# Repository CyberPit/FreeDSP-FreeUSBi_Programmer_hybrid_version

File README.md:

# FreeDSP-FreeUSBi_Programmer_hybrid_version　　

This is another PCB layout design of FreeUSBi.  
Component Layout had changed, Voltage-shifter design changed, selectable parts type capability (SMD or TH)
Please see the images in the "Photo" directory for differences.  
  
## Issue found on some CY7C68013A boards.
Some CY7C68013A boards can not boot when connected to a FreeUSBi board. The reason is that the SDA line of the I2C bus voltage dropped during the boot sequence. The Voltage-Shifter circuit control line and I2C pull-up circuit were not tied to 3.3V because the uP has not run yet. So, the version 0.5 design connects them to a regulated 3.3V line. According to this change, the I2C line is pulled up to 3.3V anytime a USB is connected.  
  
## For Windows 10 users, Info:
Some machines were not able to run the official FreeUSBi driver.  
But a few machines have succeeded in installing & running with the 3eAudio version FreeUSBi driver (Located at https://www.3e-audio.com/dsp/adau1701-2in4out/)

# License
This work and all other materials under https://github.com/freeDSP are licensed under a Creative Commons Attribution Share-Alike 4.0 license. This allows for both personal and commercial derivative works, as long as they credit freeDSP and release their designs under the same license.

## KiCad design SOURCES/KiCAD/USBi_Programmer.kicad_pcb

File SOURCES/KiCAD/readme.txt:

Here is another version of FreeUSBi.
- Same Function
- New Layout PCB
- Selectable SMD/TH resisitors

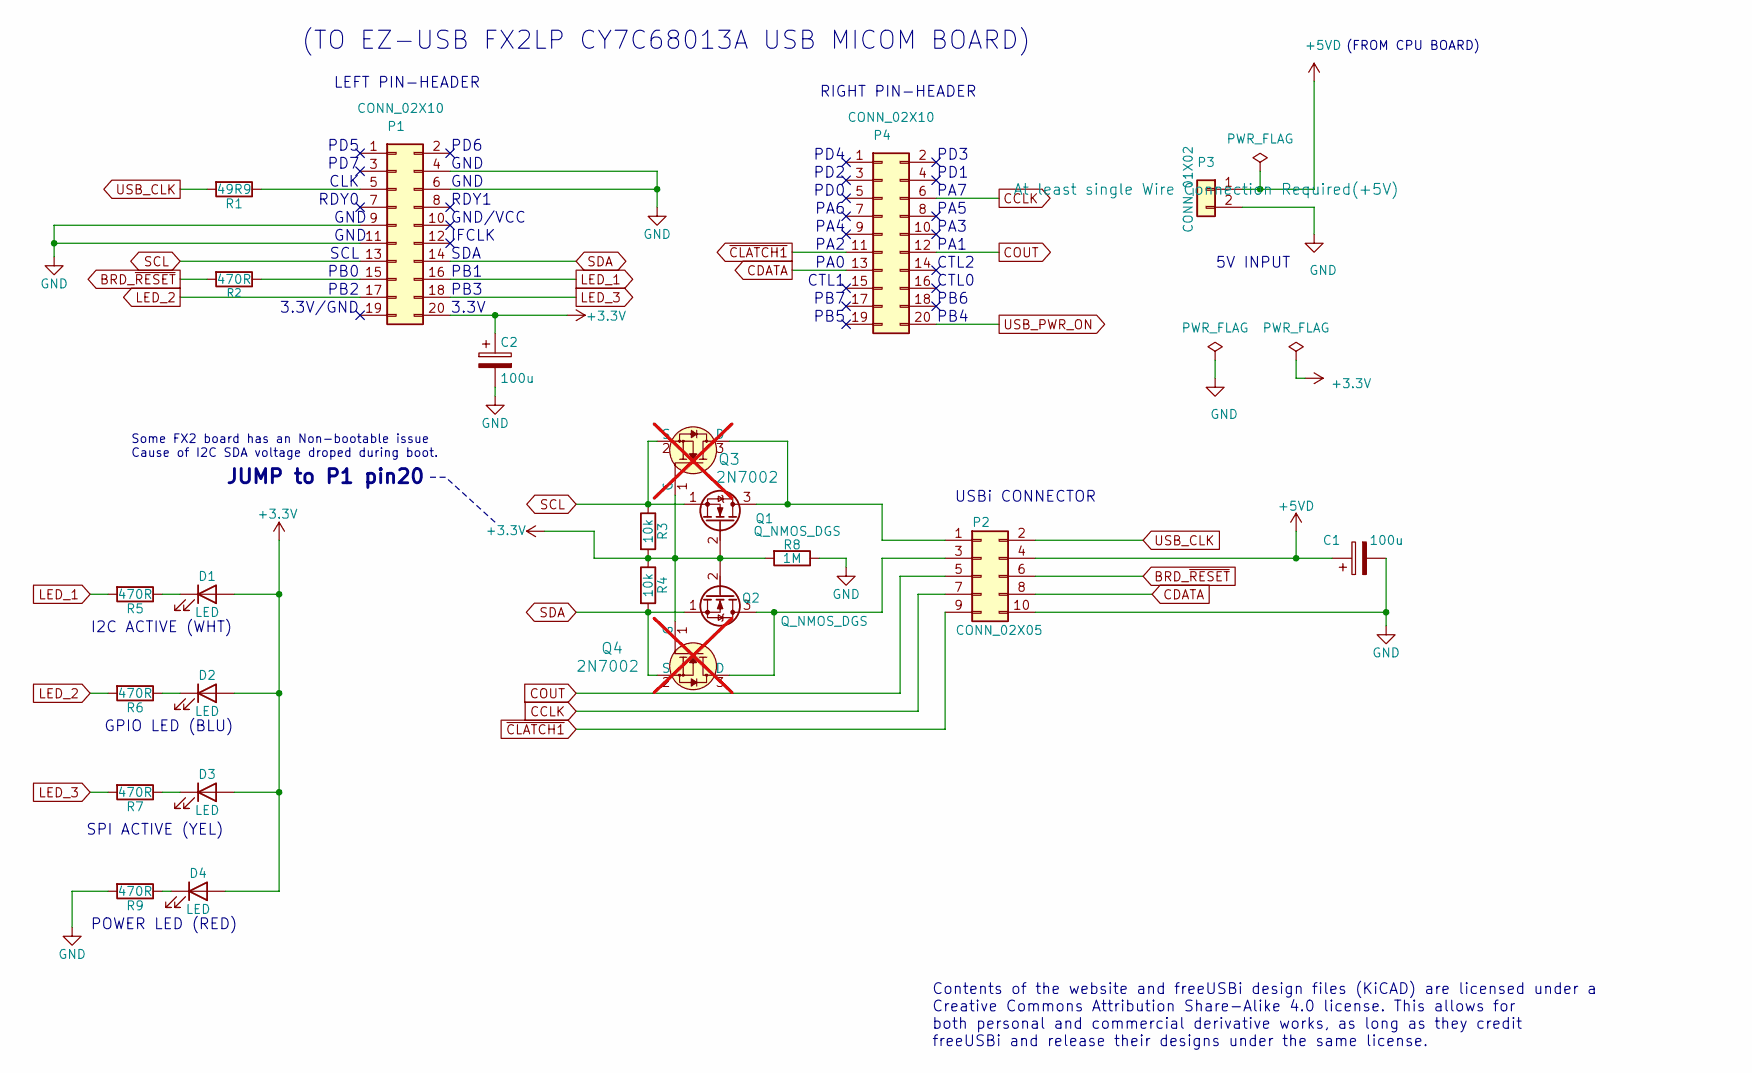
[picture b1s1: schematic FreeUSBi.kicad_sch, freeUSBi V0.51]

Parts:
C1, C2: 100u; Elko_vert_11.2x6.3mm_RM2.5_CopperClear
D1, D2, D3, D4: LED; LED_D3.0mm
P1, P4: CONN_02X10; Pin_Header_Straight_2x10
P2: CONN_02X05; IDC_Header_Straight_10pins
P3: CONN_01X02; Pin_Header_Straight_1x02
Q1, Q2: Q_NMOS_DGS; TO-92_Inline_Narrow_Oval
Q3, Q4: 2N7002; SOT-23-3; MPN 2N7002; Digi-Key_PN 2N7002NCT-ND; not fitted
R1: 49R9; Resistor_SMD+THTuniversal_0603to0805_RM7.5_HandSoldering_Re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
R2, R5, R6, R7, R9: 470R; Resistor_SMD+THTuniversal_0603to0805_RM7.5_HandSoldering_Re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
R3, R4: 10k; Resistor_SMD+THTuniversal_0603to0805_RM7.5_HandSoldering_Re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
R8: 1M; Resistor_SMD+THTuniversal_0603to0805_RM7.5_HandSoldering_Re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

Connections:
+5VD: C1.1, P2.4, P3.1
BRD_~RESET: P2.6, R2.2
CCLK: P2.7, P4.6
CDATA: P2.8, P4.13
COUT: P2.5, P4.12
GND: C1.2, C2.2, P1.4, P1.6, P1.9, P1.11, P2.10, P3.2, R8.1, R9.2
LED_1: P1.16, R5.2
LED_2: P1.17, R6.2
LED_3: P1.18, R7.2
unnamed: D1.1 (K), R5.1
unnamed: D2.1 (K), R6.1
unnamed: D3.1 (K), R7.1
unnamed: D4.1 (K), R9.1
unnamed: P1.5, R1.1
unnamed: P1.15, R2.1
unnamed: P2.1, Q1.3 (D), Q3.3 (D)
unnamed: P2.3, Q2.3 (D), Q4.3 (D)
SCL: P1.13, Q1.1 (S), Q3.2 (S), R3.1
SDA: P1.14, Q2.1 (S), Q4.2 (S), R4.2
USB_CLK: P2.2, R1.2
USB_PWR_ON: P4.20
~CLATCH1: P2.9, P4.11

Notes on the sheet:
POWER LED (RED)
IFCLK
Contents of the website and freeUSBi design files (KiCAD) are licensed under a Creative Commons Attribution Share-Alike 4.0 license. This allows for both personal and commercial derivative works, as long as they credit freeUSBi and release their designs under the same license.
PA5
PB4
PD1
PA7
PB1
GND
GND/VCC
RDY0
PA4
3.3V
PB2
I2C ACTIVE (WHT)
CTL2
SCL
3.3V/GND
(TO EZ-USB FX2LP CY7C68013A USB MICOM BOARD)
PD0
PB6
PB5
CTL1
USBi CONNECTOR
PB0
PA1
PA0
PA3
JUMP to P1 pin20
(FROM CPU BOARD)
PD5
PD2
5V INPUT
SDA
SPI ACTIVE (YEL)
PB3
Some FX2 board has an Non-bootable issue Cause of I2C SDA voltage droped during boot.
PA2
PD6
GPIO LED (BLU)

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
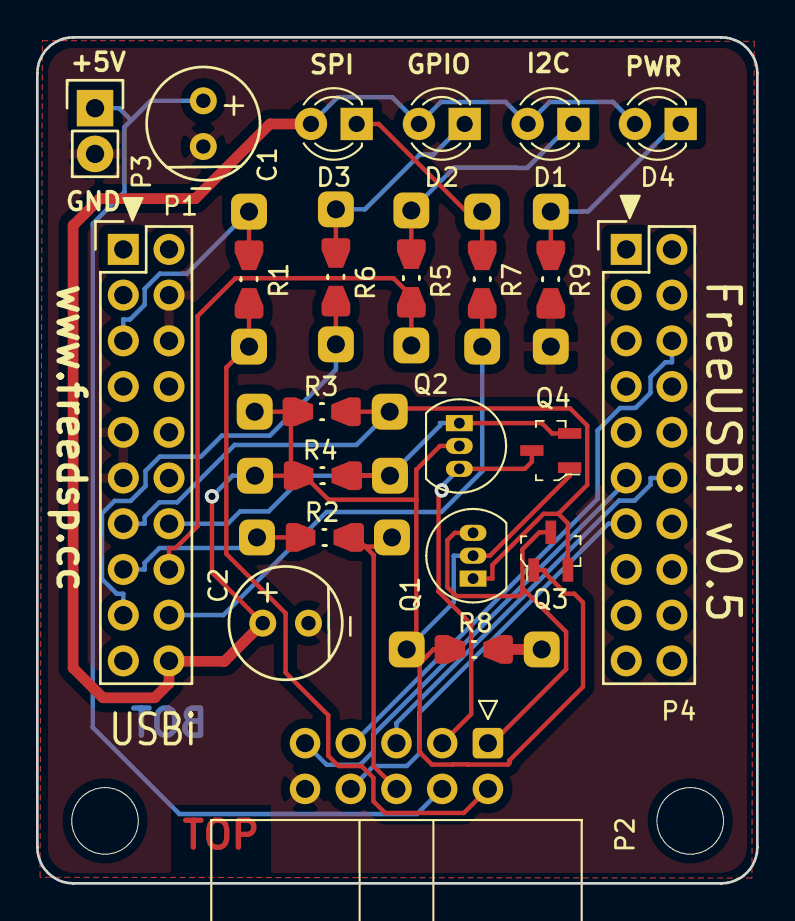
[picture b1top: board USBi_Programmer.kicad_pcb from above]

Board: 2 copper layers, 40.0 x 47.0 mm, 23 parts (0 on the bottom side), 22 nets.

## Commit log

2025-05-02 Gerber and Drill File
2025-05-02 Verion 0.5 update Release

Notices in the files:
SOURCES/KiCAD/FreeUSBi.kicad_sch:
www.creativecommons.org/licenses/by-sa/4.0/legalcode
